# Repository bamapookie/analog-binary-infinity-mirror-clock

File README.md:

# Analog Binary Infinity Mirror Clock

Plans, parts, and code for building your very own clock that no one can read. (Except you... maybe.)

> **Status:** Resurrecting an abandoned build. The firmware targets an Adafruit
> ItsyBitsy M4 (SAMD51) driving six APA102/DotStar rings, disciplined by a GPS
> module so it never needs to be set. See [`ROADMAP.md`](ROADMAP.md) for what's
> planned next (library extraction, a desk-sized revision, and magnet-based
> configuration). Project boards on [CADLAB.io](https://cadlab.io/project/2407).

## The Concept

Everyone knows analog clocks--2 or 3 hands moving around a clock face, indicating hours, minutes, and sometimes
seconds. It is easy to get a sense of time progressing by watching the hands move around, or gauging the position of one
hand in relation to the numbers (or even just the angles) to fill in an appropriate sense of precision.

Most people have seen binary clocks--Several obscure lights flickering on and off in a seemingly random pattern with
no markings to indicate number groupings, then having to decode the lights into a usable number. Some people cheat and
use Binary Coded Decimal in order to only have to decode one digit at a time.

What the world really needs is a way to combine the obscurity and complexity of decoding a binary number into a usable
format with the intrinsic sense of progress you get from the movement of the hands of an analog clock.

Thus began my quest to build a Binary Analog Clock! 11 hands moving around a clock face with only a '0' and a '1' to
adorn it. Now how the #^%\$% am I going to build a clock with 11 hands? I searched Google. Couldn't find anything
remotely resembling a kit for building an 11 handed clock. (IKR?) So I sat on it for a while, then I saw an infinity
mirror with NeoPixels in it, and it clicked. The infinity mirror effect could look like a line, and radiating in from
pixels on the outer ring, it could look like a hand. I finally had my plan. I dropped a boatload of money on Adafruit
and my local MicroCenter (See the materials list below, and thanks LadyAda for having such a fantastic operation.) and
started to work.

## The Plan

#### Basic plan

Basically, an infinity mirror is made with two mirrors facing each other. The mirror closest to you is semi-transparent.
This allows some of the light through, but the rest of the light bounces back and repeats the process. This makes the
space between the mirrors appear to extend beyond the back mirror. Between the mirrors, we will place 6 concentric
circles of DotStar pixels facing inward. Each of these will be a "hand" representing one bit of the binary number.
All six rings will be used to indicate minutes (2^6 = 64 > 60). The five innermost circles will also indicate hours
(2^5 = 32 > 24), using a slightly wider hand to distinguish it from the minute hands. I also have a plan for indicating
seconds by having the seconds "ripple" out from the corresponding minute hands, making the clock even more unreadable.

#### Intermediate plan

We want the "mechanics" to be small, so we'll use an Itsy Bitsy M4 to drive everything with a few other chips to bring up
the logic voltage to the DotStars. We'll print PCBs to mount it all on and stick it behind the clock.

#### Complex Plan

This is a clock. Clocks, in their default state, only blink 001100:000000 over and over again. We don't want that! We
want a clock that keeps its time. Moreover, we don't want to have to set it. Ever. Let's throw a GPS on there and we
won't ever have to set it! We'll just need to spend and extra few weeks figuring out the GPS code, how to set the time
from it, and wait... GPS time isn't the same as UTC time? UTC time has leap seconds? The standard time library
doesn't handle leap seconds or milliseconds? This won't do.

#### Overly Complex Plan

Let's rewrite the Arduino Time libraries, the GPS libraries, and the TimeZone libraries to handle leap seconds and
milliseconds. And because I laugh at my own jokes, we'll make it blink 001100:000000 for a little while when we turn
it on.

Okay. Maybe that is overdoing it. How about we keep track of the seconds separately, and just use the time libraries
for minute-level precision. We will increment the seconds using the PPS signal and data from the GPS on when leap
seconds occur, then update the GPS time when we determine a minute rollover has occured. This will also handle the
delay between the actual start of a second and the time that the NMEA message containing the time arrives from the GPS.

## The Implementation

Parts acquired... let's go!

While the final product will use an Itsy Bitsy M4 Express, I'm prototyping it with a Feather M4 Express. When I get the
IBM4, I'll use the Feather M4 Express along with an OLED display and another chip to measure the power usage of the
DotStars to make sure I have the right size power supply.

So now I have the breadboard out with one freshly soldered Feather M4 Express, one freshly soldered GPS Breakout board,
and a 1 meter length DotStar Strip.

#### Phase 1 - Testing the components

Using the default strandtest.ino from Adafruit with minor modifications, I tested out the DotStar strips. (See the
[`examples/`](examples/) folder for the strand and GPS bring-up sketches.)

PPS Test

GPS Test

#### Phase 2 - Hardware

Designing the PCB
Designing the Frame

#### Phase 3 - Writing the code

## Useful Links

##### Parts Lists

- https://www.adafruit.com/wishlists?wid=482342

##### Microcontrollers

- https://learn.adafruit.com/adafruit-feather-m4-express-atsamd51/overview
- https://learn.adafruit.com/introducing-adafruit-itsybitsy-m4/overview

##### Programming (C, C++)

- https://www.arduino.cc/reference/en/#functions
- http://www.gammon.com.au/forum/?id=11488
- https://forum.arduino.cc/index.php?topic=503368.0
- https://create.arduino.cc/projecthub/GadgetsToGrow/don-t-delay-use-an-arduino-task-scheduler-today-215cfe
- https://github.com/arkhipenko/TaskScheduler

##### DotStars

- https://learn.adafruit.com/adafruit-dotstar-leds/overview
- https://github.com/adafruit/Adafruit_DotStar
- https://wp.josh.com/2015/12/22/getting-real-using-blind-send-spi-to-turbocharge-the-adafruit-dotstar-library/

##### FastLED

- https://fastled.io/
- https://github.com/FastLED/FastLED
- https://www.reddit.com/r/FastLED/

##### GPS

- http://www.hhhh.org/wiml/proj/nmeaxor.html
- http://aprs.gids.nl/nmea/
- http://arduiniana.org/libraries/tinygpsplus/
- https://github.com/mikalhart/TinyGPSPlus
- http://www.flytron.com/pdf/MTK_commands.pdf
- https://en.wikipedia.org/wiki/NMEA_0183

###### Adafruit Ultimate GPS Breakout Board

- https://github.com/adafruit/Adafruit_GPS
- https://learn.adafruit.com/adafruit-ultimate-gps/overview
- https://forums.adafruit.com/viewtopic.php?f=19&t=148591&p=734292#p733660
- https://cdn-shop.adafruit.com/datasheets/GlobalTop-FGPMMOPA6C-Datasheet-V0A-Preliminary.pdf
- https://cdn-shop.adafruit.com/datasheets/PMTK_A11.pdf
- http://www.alphamicrowireless.com/franchises/globaltop-technology/pa6h.aspx

###### SparkFun GPS Breakout - XA1110

- https://www.sparkfun.com/products/14414
- https://www.sparkfun.com/datasheets/GPS/Modules/PMTK_Protocol.pdf

##### Components
- https://learn.sparkfun.com/tutorials/capacitors/all

##### Time

- https://www.pjrc.com/teensy/td_libs_Time.html
- https://www.davidpilling.com/wiki/index.php/GPS#a6
- https://github.com/PaulStoffregen/Time
- https://forum.arduino.cc/index.php?topic=503368.0
- https://github.com/JChristensen/Timezone

##### PCBs

- https://www.autodesk.com/products/eagle/free-download
- https://learn.adafruit.com/making-pcbs-with-oshpark-and-eagle/ordering-and-assembly
- https://oshpark.com/
- http://kicad-pcb.org/download/windows/
- https://cadlab.io ([My project](https://cadlab.io/project/2407)). 

##### Soldering

- https://www.youtube.com/watch?v=VxMV6wGS3NY

##### Random

- https://arduino.stackexchange.com/questions/348/how-to-organize-my-arduino-projects-structure-for-easy-source-control
- http://www.gammon.com.au/forum/?id=11488

## Addendum
#### Leap Seconds
During testing of the GPS is when I discovered the possible occurrence of leap seconds.  Every couple of years, or so, 
an extra second (or 2) is added to (or removed from) the last minute of June or December, UTC.  So instead of the 
seconds counting 58, 59, 60/0, 1, 2, etc., they might add an extra second (59, 60, 61/0, 1, 2), an extra 2 seconds 
(59, 60, 61, 62/0, 1, 2), or take away a second (58, 59/0, 1, 2).  All of this is to keep UTC in sync with UT1, which is 
the actual time based on the position of the earth in relation to the position of the stars.   UT1 drifts due to tidal 
forces changing the speed that the earth rotates.  Whenever the difference between UTC and UT1 reaches .9 seconds, leap 
seconds are used to correct the imbalance.

Unix clocks usually just ignore this.  They just leave the time at 23:59:59 until 00:00:00 eventually gets here.  All of
the time libraries used in Arduino environments also ignore this, and make no attempt to handle it.

## Repository Layout

- `src/` — the clock firmware (`main.cpp`).
- `lib/` — project libraries: board pin maps (`abimc_pcb`) and GPS command sets (`xa1110`, `mtk33x9`).
- `examples/` — standalone bring-up sketches for the LEDs and GPS (see [`examples/README.md`](examples/README.md)).
- `test/` — reserved for PlatformIO unit tests.
- `pcb/` — Autodesk EAGLE schematic and board files.
- `images/` — clock-face artwork (SVG/XCF).

## Building

This is a [PlatformIO](https://platformio.org/) project. With the PlatformIO CLI installed:

```sh
pio run                 # build the firmware
pio run --target upload # flash a connected ItsyBitsy M4
pio device monitor      # open the serial monitor
```

## License

Dual-licensed: firmware under the MIT License, hardware (PCB and artwork) under
CERN-OHL-S v2. See [`LICENSE.md`](LICENSE.md) for details.

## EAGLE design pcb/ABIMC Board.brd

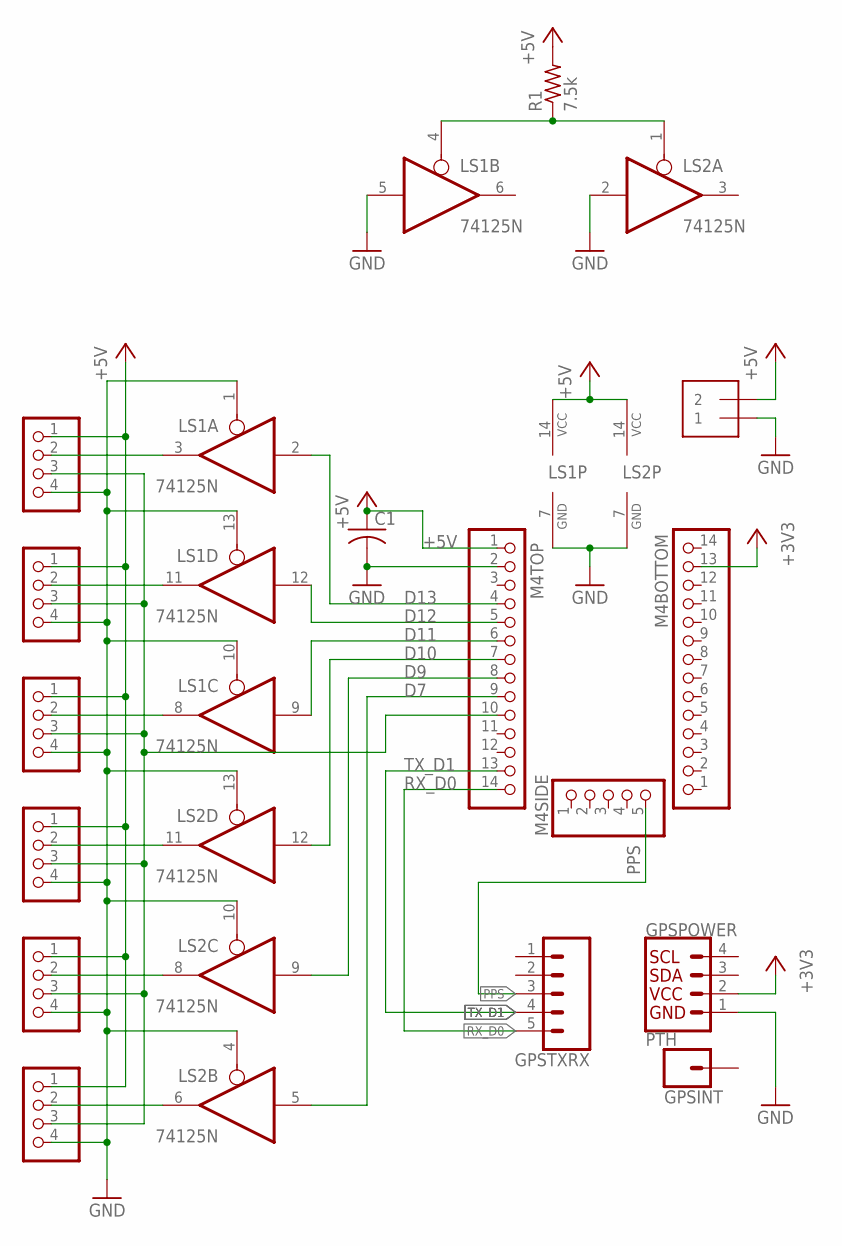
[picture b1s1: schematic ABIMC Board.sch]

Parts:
C1: C-US050-024X044; C050-024X044
GPSINT: CONN_01PTH_NO_SILK_YES_STOP; 1X01_NO_SILK
GPSPOWER: PTH; 1X04_NO_SILK
GPSTXRX: CONN_05NO_SILK; 1X05_NO_SILK
JP1, JP2, JP3, JP4, JP5, JP6: PINHD-1X4/90; 1X04/90
LS1, LS2: 74125N; DIL14
M4BOTTOM, M4TOP: HEADER-1X14; 1X14_ROUND70
M4SIDE: HEADER-1X570MIL; 1X05_ROUND_70
POWER: 1X2-3.5MM
R1: 7.5k; 0204/7

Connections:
+3V3: GPSPOWER.2 (VCC), M4BOTTOM.13
+5V: C1.1, JP1.1, JP2.1, JP3.1, JP4.1, JP5.1, JP6.1, LS1.14 (VCC), LS2.14 (VCC), M4TOP.1, POWER.2, R1.2
D7: LS2.5 (I), M4TOP.9
D9: LS2.9 (I), M4TOP.8
D10: LS2.12 (I), M4TOP.7
D11: LS1.9 (I), M4TOP.6
D12: LS1.12 (I), M4TOP.5
D13: LS1.2 (I), M4TOP.4
DSDATA: JP1.3, JP2.3, JP3.3, JP4.3, JP5.3, JP6.3, M4TOP.10
GND: C1.2, GPSPOWER.1 (GND), JP1.4, JP2.4, JP3.4, JP4.4, JP5.4, JP6.4, LS1.1 (OE), LS1.5 (I), LS1.7 (GND), LS1.10 (OE), LS1.13 (OE), LS2.2 (I), LS2.4 (OE), LS2.7 (GND), LS2.10 (OE), LS2.13 (OE), M4TOP.2, POWER.1
unnamed: JP1.2, LS1.3 (O)
unnamed: JP2.2, LS1.11 (O)
unnamed: JP4.2, LS2.11 (O)
unnamed: JP5.2, LS2.8 (O)
unnamed: JP6.2, LS2.6 (O)
unnamed: JP3.2, LS1.8 (O)
PPS: GPSTXRX.3, M4SIDE.5
RX_D0: GPSTXRX.5, M4TOP.14
TX_D1: GPSTXRX.4, M4TOP.13
VHI: LS1.4 (OE), LS2.1 (OE), R1.1

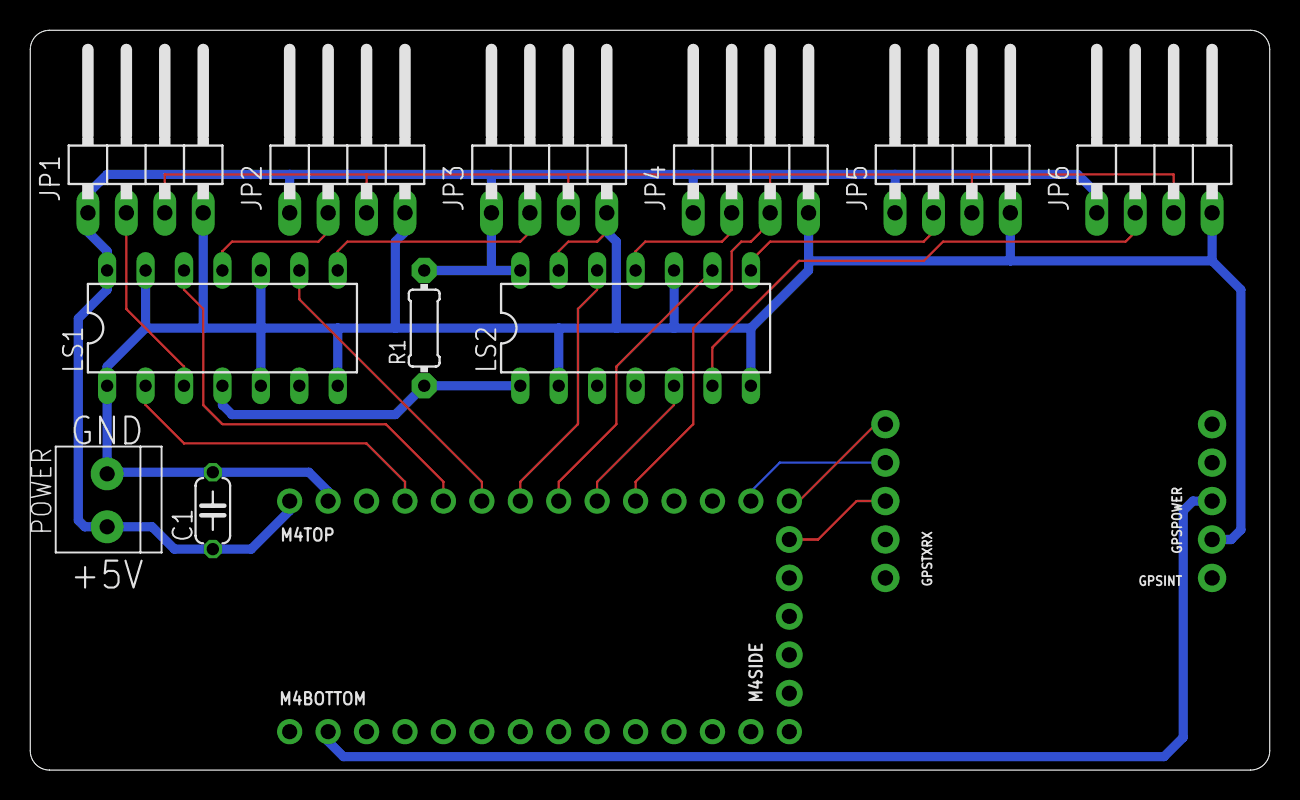
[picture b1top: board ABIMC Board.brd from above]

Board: 2 copper layers, 81.9 x 48.9 mm, 17 parts (0 on the bottom side), 20 nets.

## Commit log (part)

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2020-01-09 Backlink to CADLAB.io has been added.
2020-01-14 Readme updates
2020-01-22 Big update!
    Revamped the tests, showing the progression of the development.
    Updates to the PCB, including getting the clock and data pins in the right order.
    Moved some stuff to lib directory (Need to create issue to modularize these)
    Known bugs (Need to create issues for these):
    When hand moves into new pixel, the pixel sometimes flashes.
    Complete power cycle loses connection to GPS. Reset fixes.
2020-01-24 Updating tests to use all 6 strands now that I have the last two wired up
2020-01-24 Add last two strands
2020-01-27 Use 255 pixels instead of 256, fix fade in/fade out flash
    Fixes #2
2020-01-27 Cycle colors through the spectrum once every 8 seconds
    Fixes #5
2020-01-27 Cycle colors on flashing 12 as well.
    #5
2020-01-27 Don't overflow the unsigned longs
    Fixes #4
    Also fixes new issue where hand overlapping strand boundary would show up on other strand.
    Also fixes hour hand showing up where not configured (6th strand)

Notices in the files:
parts and their libraries:
microbuilder: This work is placed in the public domain, and may be freely used for commercial and non-commercial work with the following conditions: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
SparkFun-Connectors: Licensing: Creative Commons ShareAlike 4.0 International - https://creativecommons.org/licenses/by-sa/4.0
